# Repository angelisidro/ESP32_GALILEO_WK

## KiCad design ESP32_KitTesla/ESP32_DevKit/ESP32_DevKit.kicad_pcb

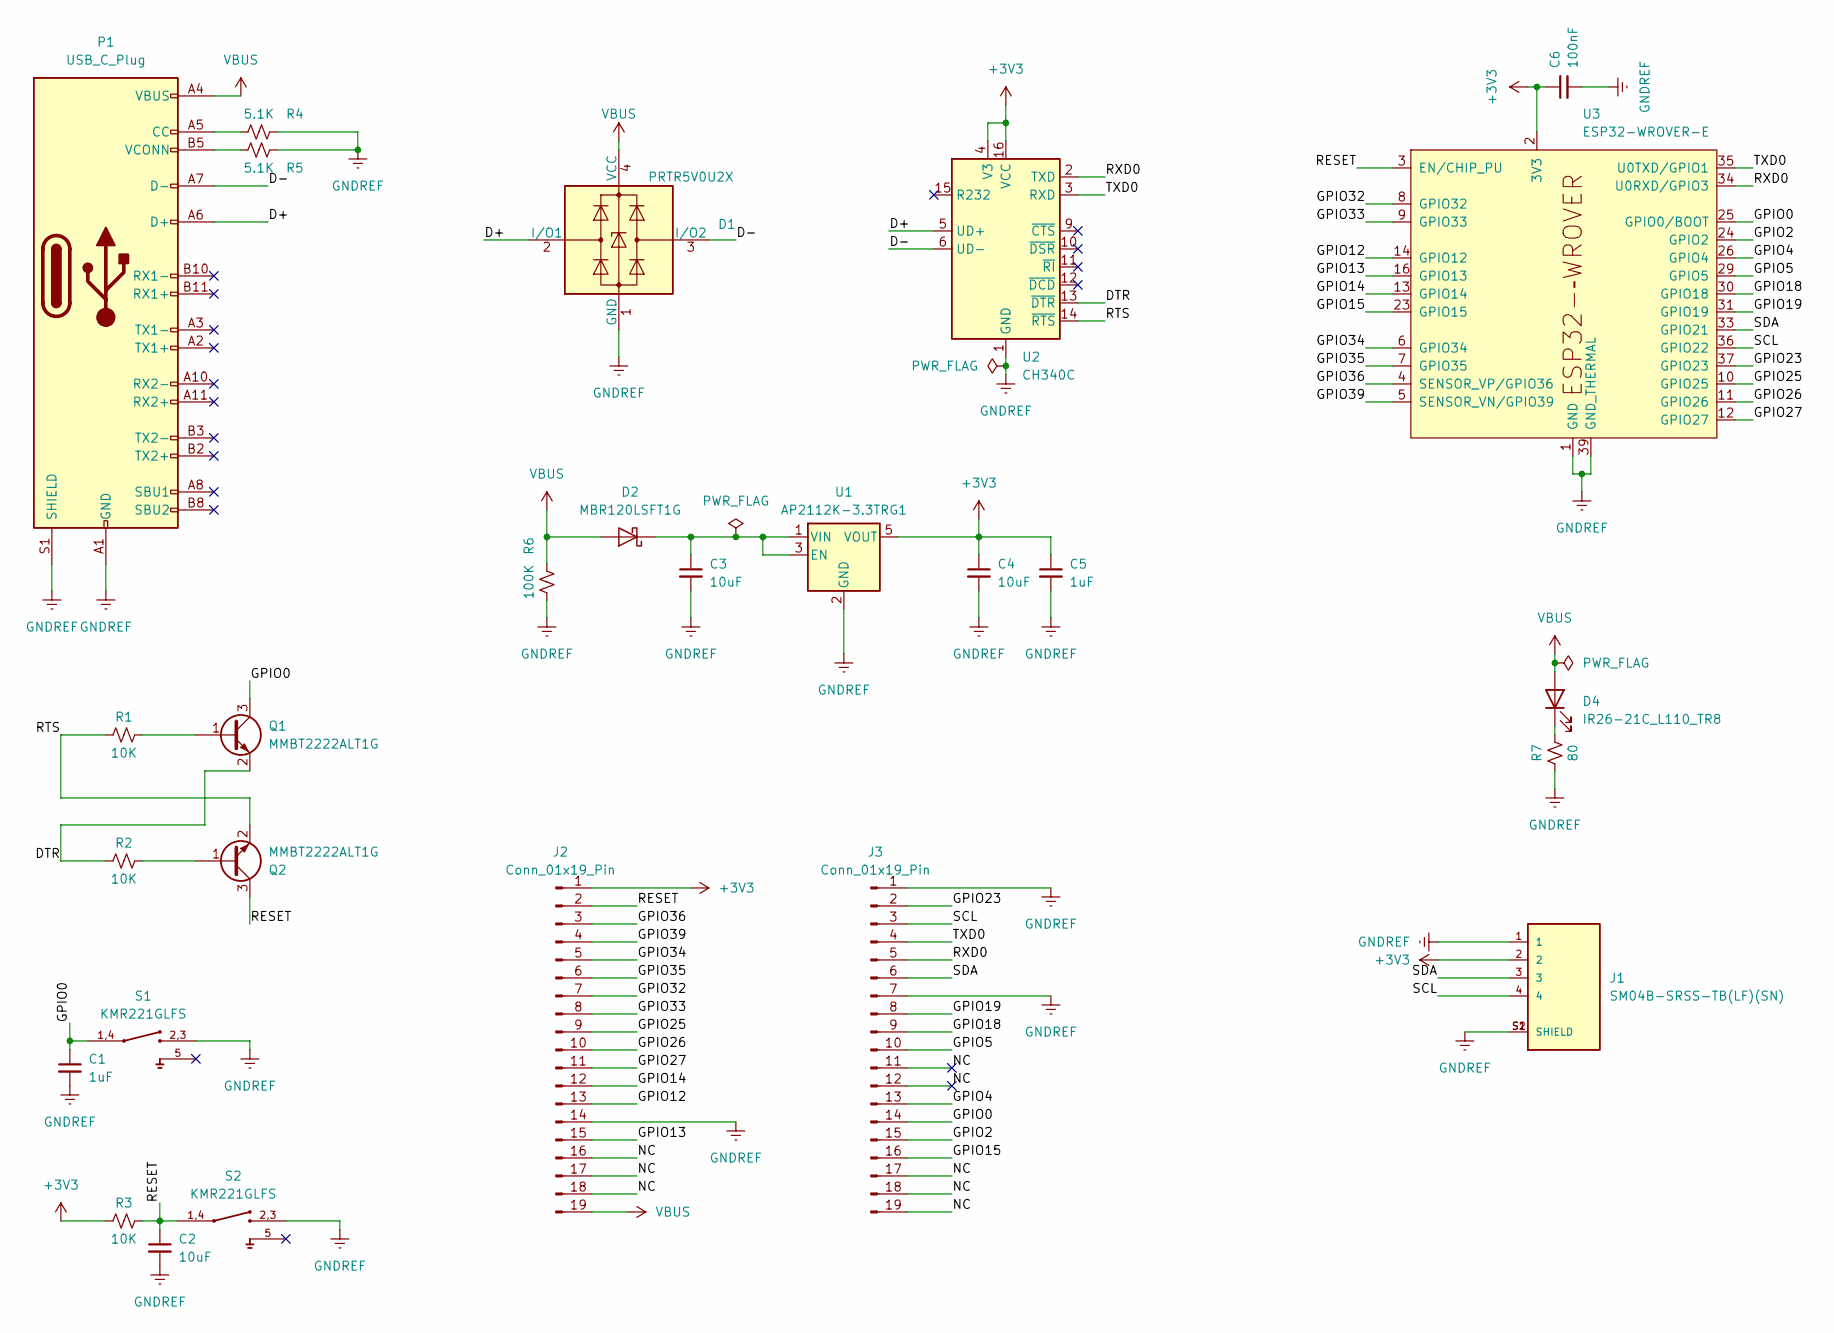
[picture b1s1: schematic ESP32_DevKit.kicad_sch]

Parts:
C1, C5: 1uF; C_0805_2012Metric_Pad1.18x1.45mm_HandSolder
C2, C3, C4: 10uF; C_0805_2012Metric_Pad1.18x1.45mm_HandSolder
C6: 100nF; C_0805_2012Metric_Pad1.18x1.45mm_HandSolder
D1: PRTR5V0U2X; SOT-143
D2: MBR120LSFT1G; D_SOD-123F
D4: IR26-21C_L110_TR8; LED_1206_3216Metric_Pad1.42x1.75mm_HandSolder
J1: SM04B-SRSS-TB(LF)(SN); JST_SM04B-SRSS-TB(LF)(SN)
J2, J3: Conn_01x19_Pin; PinHeader_1x19_P2.54mm_Vertical
P1: USB_C_Plug; USB_C_Receptacle_XKB_U262-16XN-4BVC11
Q1, Q2: MMBT2222ALT1G; SOT-23-3
R1, R2, R3: 10K; R_0805_2012Metric_Pad1.20x1.40mm_HandSolder
R4, R5: 5.1K; R_0805_2012Metric_Pad1.20x1.40mm_HandSolder
R6: 100K; R_0805_2012Metric_Pad1.20x1.40mm_HandSolder
R7: 80; R_0805_2012Metric_Pad1.20x1.40mm_HandSolder
S1, S2: KMR221GLFS; SW_KMR221GLFS
U1: AP2112K-3.3TRG1; SOT-23-5
U2: CH340C; SOIC-16_3.9x9.9mm_P1.27mm
U3: ESP32-WROVER-E

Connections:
+3V3: C4.1, C5.1, C6.1, J1.2, J2.1, R3.2, U1.5 (VOUT), U2.4 (V3), U2.16 (VCC), U3.2 (3V3)
/D+: D1.2 (I/O1), P1.A6 (D+), P1.B6, U2.5 (UD+)
/D-: D1.3 (I/O2), P1.A7 (D-), P1.B7, U2.6 (UD-)
/DTR: Q1.2 (E), R2.2, U2.13 (~DTR)
/GPIO0: C1.1, J3.14, Q1.3 (C), S1., S1.1,4, U3.25 (GPIO0/BOOT); also elsewhere on the board
/GPIO2: J3.15, U3.24 (GPIO2)
/GPIO4: J3.13, U3.26 (GPIO4)
/GPIO5: J3.10, U3.29 (GPIO5)
/GPIO12: J2.13, U3.14 (GPIO12)
/GPIO13: J2.15, U3.16 (GPIO13)
/GPIO14: J2.12, U3.13 (GPIO14)
/GPIO15: J3.16, U3.23 (GPIO15)
/GPIO18: J3.9, U3.30 (GPIO18)
/GPIO19: J3.8, U3.31 (GPIO19)
/GPIO23: J3.2, U3.37 (GPIO23)
/GPIO25: J2.9, U3.10 (GPIO25)
/GPIO26: J2.10, U3.11 (GPIO26)
/GPIO27: J2.11, U3.12 (GPIO27)
/GPIO32: J2.7, U3.8 (GPIO32)
/GPIO33: J2.8, U3.9 (GPIO33)
/GPIO34: J2.5, U3.6 (GPIO34)
/GPIO35: J2.6, U3.7 (GPIO35)
/GPIO36: J2.3, U3.4 (SENSOR_VP/GPIO36)
/GPIO39: J2.4, U3.5 (SENSOR_VN/GPIO39)
/NC: J2.16, J2.17, J2.18, J3.11, J3.12, J3.17, J3.18, J3.19
/RESET: C2.1, J2.2, Q2.3 (C), R3.1, S2., S2.1,4, U3.3 (EN/CHIP_PU); also elsewhere on the board
/RTS: Q2.2 (E), R1.2, U2.14 (~RTS)
/RXD0: J3.5, U2.2 (TXD), U3.34 (U0RXD/GPIO3)
/SCL: J1.4, J3.3, U3.36 (GPIO22)
/SDA: J1.3, J3.6, U3.33 (GPIO21)
/TXD0: J3.4, U2.3 (RXD), U3.35 (U0TXD/GPIO1)
GNDREF: C1.2, C2.2, C3.2, C4.2, C5.2, C6.2, D1.1 (GND), J1.1, J1.S1 (SHIELD), J1.S2 (SHIELD), J2.14, J3.1, J3.7, P1.A1 (GND), P1.A12 (GND), P1.B1 (GND), P1.B12 (GND), P1.S1 (SHIELD), R4.2, R5.2, R6.1, R7.2, S1., S1.2,3, S2., S2.2,3, U1.2 (GND), U2.1 (GND), U3.1 (GND), U3.15 (GND), U3.38 (GND), U3.39 (GND_THERMAL); also elsewhere on the board
unnamed: C3.1, D2.1 (K), U1.1 (VIN), U1.3 (EN)
unnamed: D4.1 (K), R7.1
unnamed: P1.A5 (CC), R4.1
unnamed: P1.B5 (VCONN), R5.1
unnamed: Q1.1 (B), R1.1
unnamed: Q2.1 (B), R2.1
VBUS: D1.4 (VCC), D2.2 (A), D4.2 (A), J2.19, P1.A4 (VBUS), P1.A9 (VBUS), P1.B4 (VBUS), P1.B9 (VBUS), R6.2

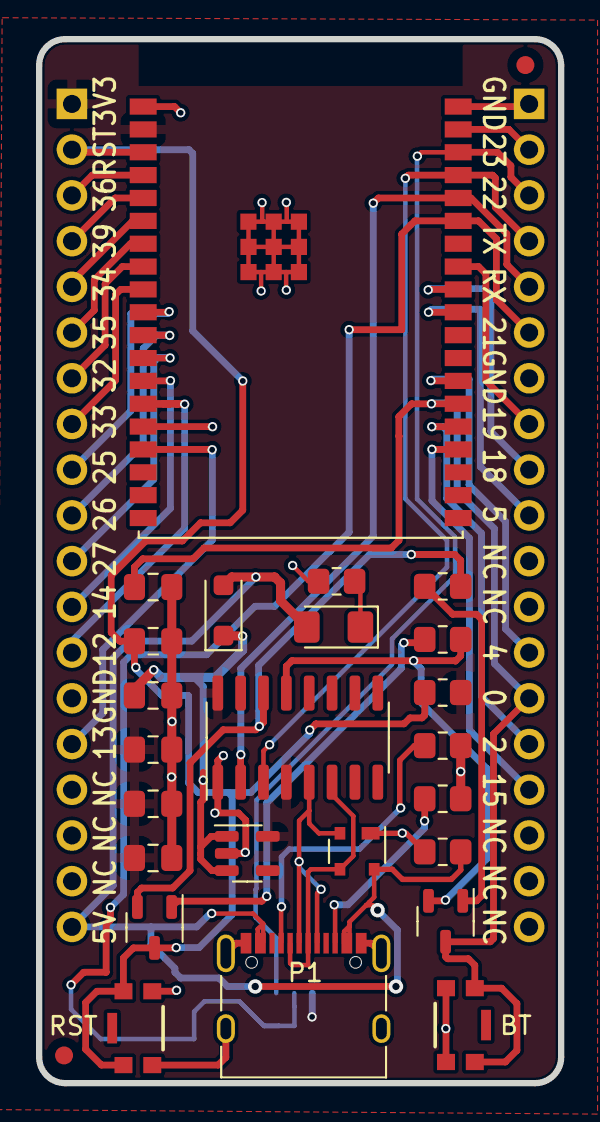
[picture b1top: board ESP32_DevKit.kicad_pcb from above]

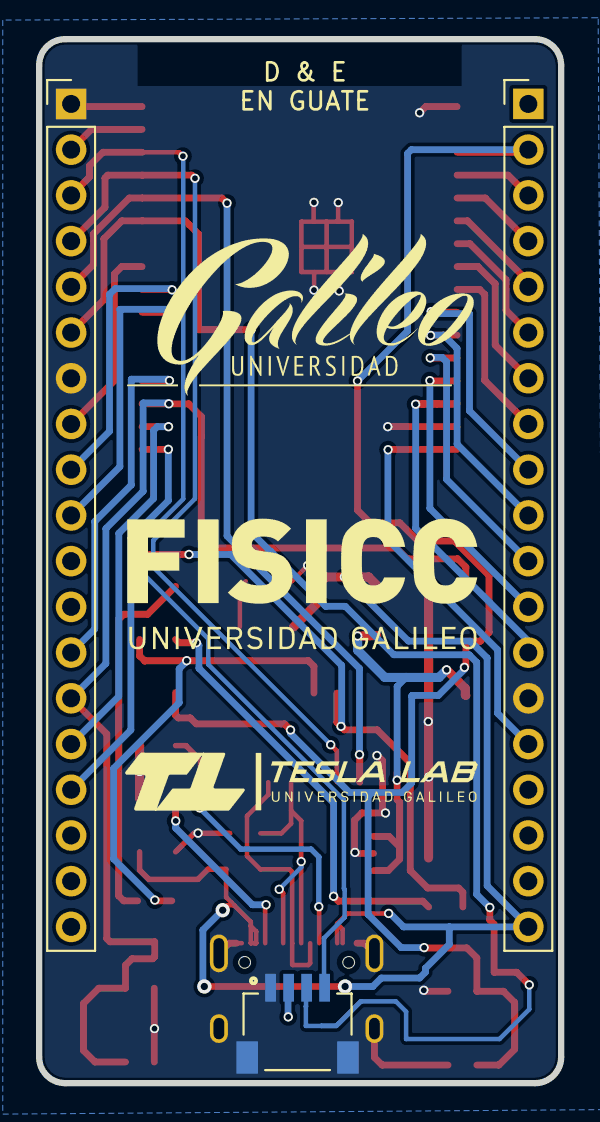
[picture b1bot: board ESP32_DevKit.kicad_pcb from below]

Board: 2 copper layers, 29.0 x 58.0 mm, 27 parts (3 on the bottom side), 39 nets.

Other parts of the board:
BT: KMR221GLFS; SW_KMR221GLFS
RST: KMR221GLFS; SW_KMR221GLFS

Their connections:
/GPIO0: BT.1, BT.4; also elsewhere on the board
/RESET: RST.1, RST.4; also elsewhere on the board
GNDREF: BT.2, BT.3, RST.2, RST.3; also elsewhere on the board

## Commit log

2024-01-09 completo
2024-01-10 ESP32_terminado
2024-10-24 FIX: silk -- nombre, BOM -- 25
